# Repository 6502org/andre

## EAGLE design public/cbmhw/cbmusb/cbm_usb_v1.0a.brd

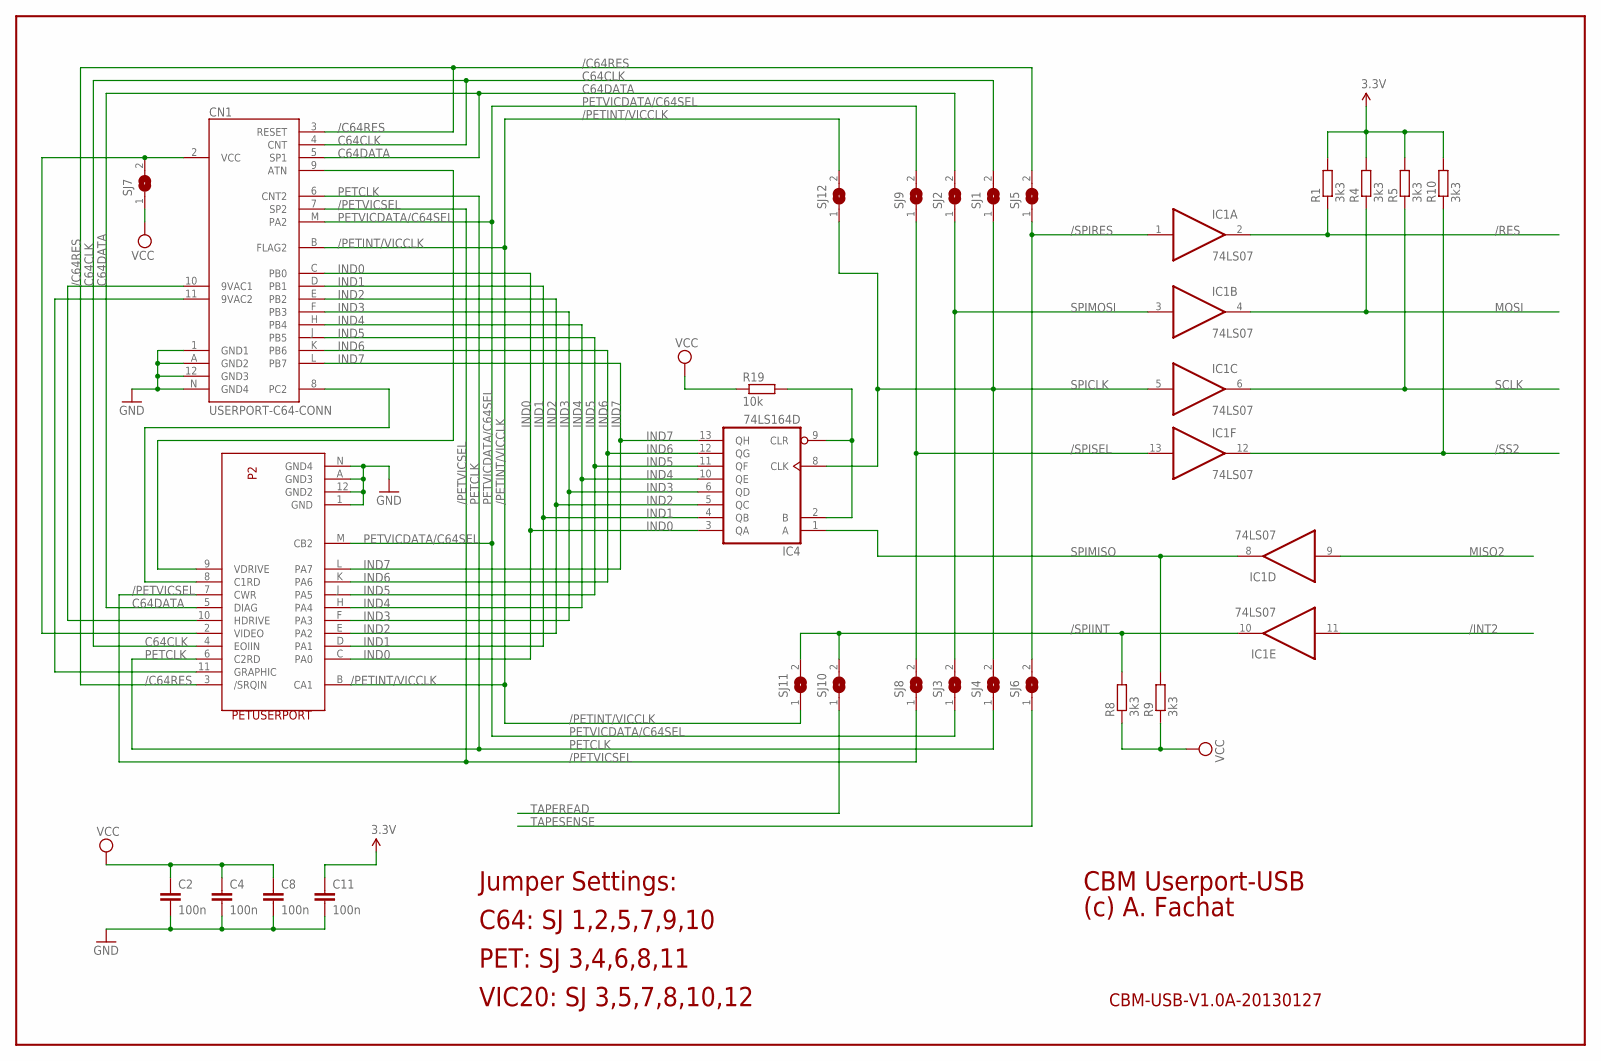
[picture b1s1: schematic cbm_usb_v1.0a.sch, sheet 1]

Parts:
C2, C4, C8, C11: 100n; C050-025X075
CN1: USERPORT-C64-CONN; UPS24CONN
IC1: 74LS07; SO14
IC4: 74LS164D; SO14
P2: PETUSERPORT; FLAT24
R1, R4, R5, R8, R9, R10: 3k3; 0204/7
R19: 10k; 0204/7
SJ1, SJ2, SJ3, SJ4, SJ5, SJ6, SJ7, SJ8, SJ9, SJ10, SJ11, SJ12: SJW

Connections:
3.3V: C11.1, R1.2, R4.2, R5.2, R10.2; also elsewhere on the board
/C64RES: CN1.3 (RESET), P2.3 (/SRQIN), SJ5.2
/INT2: IC1.11 (I); also elsewhere on the board
/PETINT/VICCLK: CN1.B (FLAG2), P2.B (CA1), SJ11.1, SJ12.2
/PETVICSEL: CN1.7 (SP2), P2.7 (CWR), SJ8.1
/RES: IC1.2 (O), R1.1; also elsewhere on the board
/SPIINT: IC1.10 (O), R8.2, SJ10.2, SJ11.2
/SPIRES: IC1.1 (I), SJ5.1, SJ6.2
/SPISEL: IC1.13 (I), SJ8.2, SJ9.1
/SS2: IC1.12 (O), R10.1; also elsewhere on the board
C64CLK: CN1.4 (CNT), P2.4 (EOIIN), SJ1.2
C64DATA: CN1.5 (SP1), P2.5 (DIAG), SJ2.2
GND: C2.2, C4.2, C8.2, C11.2, CN1.1 (GND1), CN1.12 (GND3), CN1.A (GND2), CN1.N (GND4), IC1.7 (GND), IC4.7 (GND), P2.1 (GND), P2.12 (GND2), P2.A (GND3), P2.N (GND4); also elsewhere on the board
IND0: CN1.C (PB0), IC4.3 (QA), P2.C (PA0)
IND1: CN1.D (PB1), IC4.4 (QB), P2.D (PA1)
IND2: CN1.E (PB2), IC4.5 (QC), P2.E (PA2)
IND3: CN1.F (PB3), IC4.6 (QD), P2.F (PA3)
IND4: CN1.H (PB4), IC4.10 (QE), P2.H (PA4)
IND5: CN1.J (PB5), IC4.11 (QF), P2.J (PA5)
IND6: CN1.K (PB6), IC4.12 (QG), P2.K (PA6)
IND7: CN1.L (PB7), IC4.13 (QH), P2.L (PA7)
MISO2: IC1.9 (I); also elsewhere on the board
MOSI: IC1.4 (O), R4.1; also elsewhere on the board
unnamed: CN1.10 (9VAC1), P2.10 (HDRIVE)
unnamed: CN1.11 (9VAC2), P2.11 (GRAPHIC)
unnamed: CN1.2 (VCC), P2.2 (VIDEO), SJ7.2
unnamed: CN1.8 (PC2), P2.8 (C1RD)
unnamed: CN1.9 (ATN), P2.9 (VDRIVE)
unnamed: IC4.2 (B), IC4.9 (CLR), R19.2
PETCLK: CN1.6 (CNT2), P2.6 (C2RD), SJ4.1
PETVICDATA/C64SEL: CN1.M (PA2), P2.M (CB2), SJ3.1, SJ9.2
SCLK: IC1.6 (O), R5.1; also elsewhere on the board
SPICLK: IC1.5 (I), IC4.8 (CLK), SJ1.1, SJ4.2, SJ12.1
SPIMISO: IC1.8 (O), IC4.1 (A), R9.2
SPIMOSI: IC1.3 (I), SJ2.1, SJ3.2
TAPEREAD: SJ10.1; also elsewhere on the board
TAPESENSE: SJ6.1; also elsewhere on the board
VCC: C2.1, C4.1, C8.1, IC1.14 (VCC), IC4.14 (VCC), R8.1, R9.1, R19.1, SJ7.1; also elsewhere on the board

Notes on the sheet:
CBM-USB-V1.0A-20130127
CBM Userport-USB
(c) A. Fachat
Jumper Settings:
C64: SJ 1,2,5,7,9,10
PET: SJ 3,4,6,8,11
VIC20: SJ 3,5,7,8,10,12

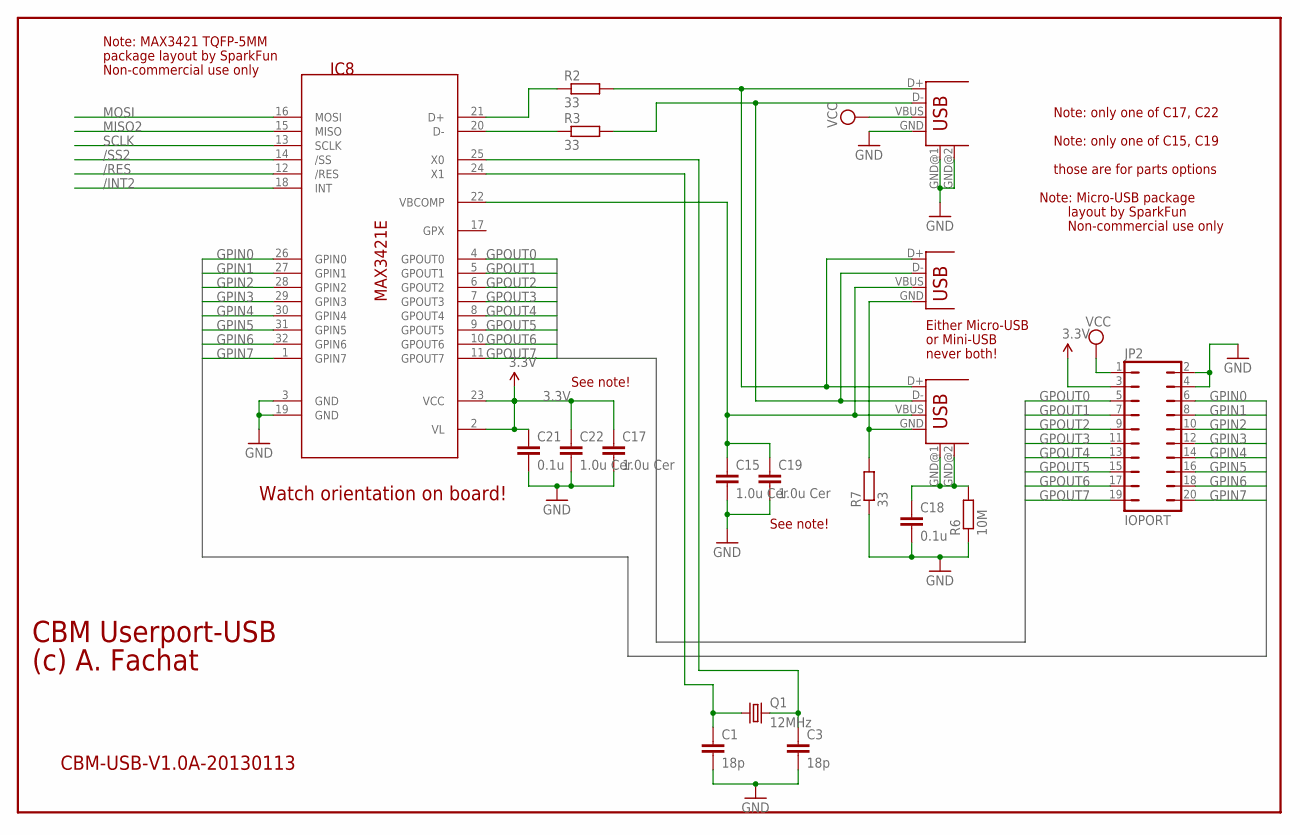
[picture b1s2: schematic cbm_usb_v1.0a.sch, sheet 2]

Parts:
C1, C3: 18p; C050-025X075
C15, C22: 1.0u Cer; C0603
C17, C19: 1.0u Cer; C050-024X044
C18, C21: 0.1u; C050-025X075
IC8: MAX3421E; TQFP32-5MM
JP2: IOPORT; JP10Q
Q1: 12MHz; HC49U70
R2, R3, R7: 33; 0204/7
R6: 10M; 0204/7
USB1: USB-A-H
USB2: USB-MB-H
X1: USB-MICROB

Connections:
3.3V: C17.1, C21.1, C22.1, IC8.2 (VL), IC8.23 (VCC), JP2.3; also elsewhere on the board
12MHZ: C1.1, IC8.24 (X1), Q1.1
/INT2: IC8.18 (INT); also elsewhere on the board
/RES: IC8.12 (/RES); also elsewhere on the board
/SS2: IC8.14 (/SS); also elsewhere on the board
GND: C1.2, C3.2, C15.2, C17.2, C18.2, C19.2, C21.2, C22.2, IC8.3 (GND), IC8.19 (GND), JP2.2, JP2.4, R6.1, R7.1, USB1.GND, USB1.GND@1 (GND), USB1.GND@2 (GND); also elsewhere on the board
GPIN0: IC8.26 (GPIN0), JP2.6
GPIN1: IC8.27 (GPIN1), JP2.8
GPIN2: IC8.28 (GPIN2), JP2.10
GPIN3: IC8.29 (GPIN3), JP2.12
GPIN4: IC8.30 (GPIN4), JP2.14
GPIN5: IC8.31 (GPIN5), JP2.16
GPIN6: IC8.32 (GPIN6), JP2.18
GPIN7: IC8.1 (GPIN7), JP2.20
GPOUT0: IC8.4 (GPOUT0), JP2.5
GPOUT1: IC8.5 (GPOUT1), JP2.7
GPOUT2: IC8.6 (GPOUT2), JP2.9
GPOUT3: IC8.7 (GPOUT3), JP2.11
GPOUT4: IC8.8 (GPOUT4), JP2.13
GPOUT5: IC8.9 (GPOUT5), JP2.15
GPOUT6: IC8.10 (GPOUT6), JP2.17
GPOUT7: IC8.11 (GPOUT7), JP2.19
MISO2: IC8.15 (MISO); also elsewhere on the board
MOSI: IC8.16 (MOSI); also elsewhere on the board
unnamed: IC8.20 (D-), R3.1
unnamed: IC8.21 (D+), R2.1
unnamed: R2.2, USB1.D+, USB2.D+, X1.D+
unnamed: R3.2, USB1.D-, USB2.D-, X1.D-
unnamed: C3.1, IC8.25 (X0), Q1.2
unnamed: R7.2, USB2.GND, X1.GND
unnamed: C18.1, R6.2, USB2.GND@1 (GND), USB2.GND@2 (GND)
SCLK: IC8.13 (SCLK); also elsewhere on the board
VBCOMP: C15.1, C19.1, IC8.22 (VBCOMP), USB2.VBUS, X1.VBUS
VCC: JP2.1, USB1.VBUS; also elsewhere on the board

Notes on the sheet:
CBM-USB-V1.0A-20130113
CBM Userport-USB
(c) A. Fachat
Either Micro-USB
or Mini-USB
never both!
Note: only one of C17, C22
Note: only one of C15, C19
those are for parts options
Watch orientation on board!
See note!
layout by SparkFun
Non-commercial use only
Note: MAX3421 TQFP-5MM
package layout by SparkFun
Note: Micro-USB package

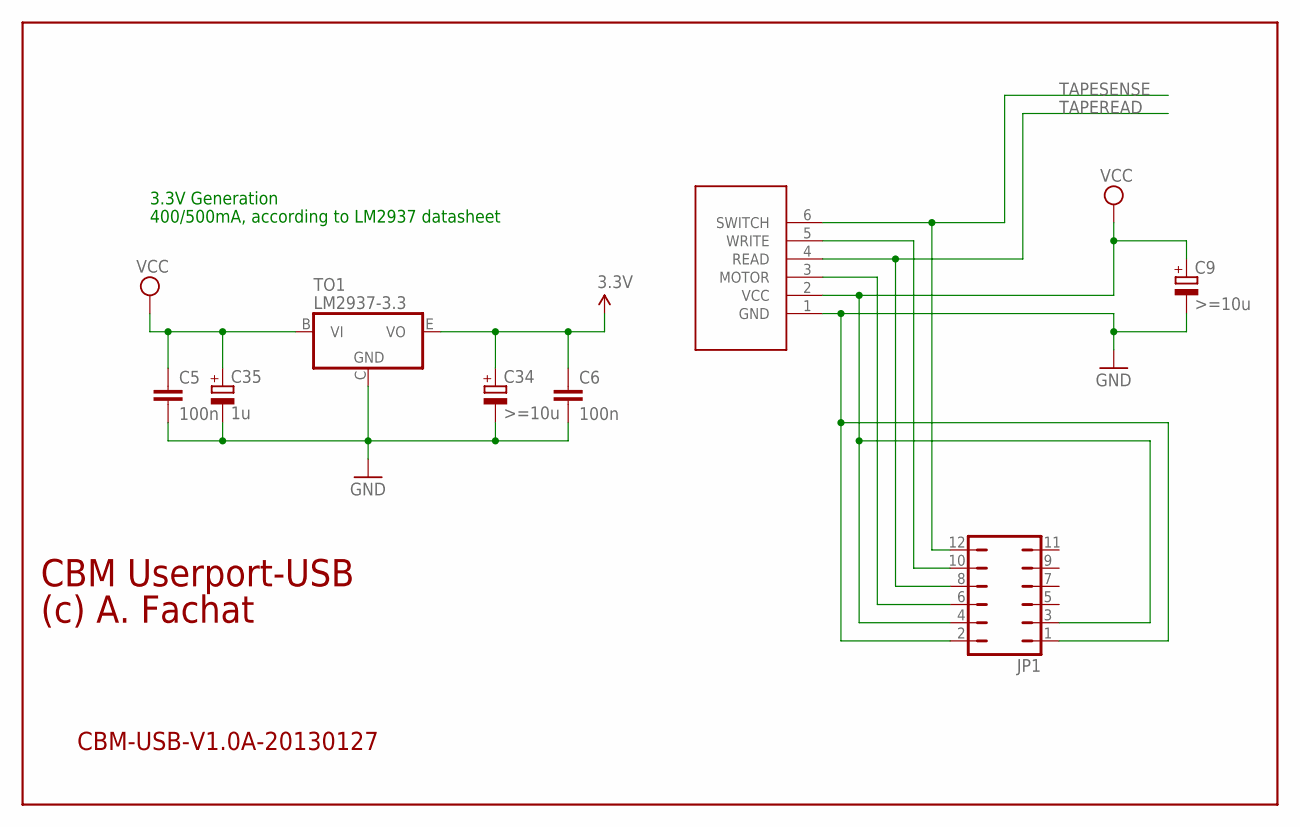
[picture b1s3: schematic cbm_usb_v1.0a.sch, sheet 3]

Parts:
C5, C6: 100n; C050-025X075
C9: >=10u; E5-10,5
C34: >=10u; E5-8,5
C35: 1u; E5-8,5
JP1: JP6Q
P3: CBMTAPE; JP6
TO1: LM2937-3.3; TO220H

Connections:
3.3V: C6.1, C34.+, TO1.E (VO); also elsewhere on the board
GND: C5.2, C6.2, C9.-, C34.-, C35.-, JP1.1, JP1.2, P3.1 (GND), TO1.C (GND); also elsewhere on the board
unnamed: JP1.6, P3.3 (MOTOR)
unnamed: JP1.10, P3.5 (WRITE)
TAPEREAD: JP1.8, P3.4 (READ); also elsewhere on the board
TAPESENSE: JP1.12, P3.6 (SWITCH); also elsewhere on the board
VCC: C5.1, C9.+, C35.+, JP1.3, JP1.4, P3.2 (VCC), TO1.B (VI); also elsewhere on the board

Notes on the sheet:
3.3V Generation
400/500mA, according to LM2937 datasheet
CBM-USB-V1.0A-20130127
CBM Userport-USB
(c) A. Fachat

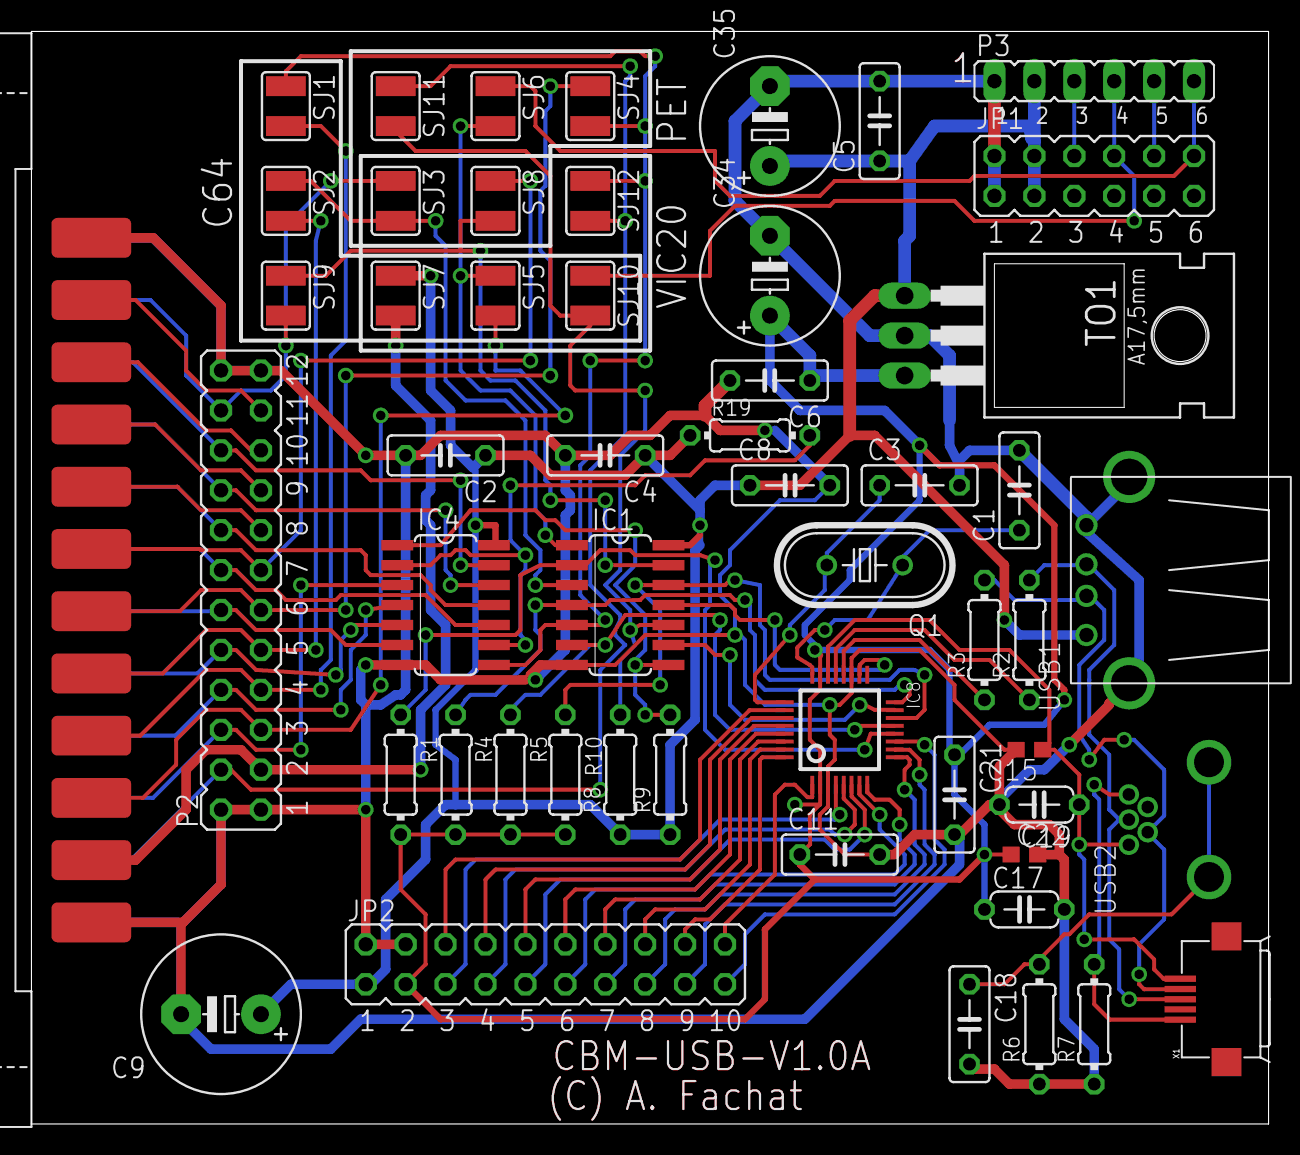
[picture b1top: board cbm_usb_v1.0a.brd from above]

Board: 2 copper layers, 78.7 x 69.5 mm, 53 parts (0 on the bottom side), 65 nets.
